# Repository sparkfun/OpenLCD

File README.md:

OpenLCD 
=========

<table class="table table-hover table-striped table-bordered">
  <tr align="center">
   <td></td>
   <td></td>
   <td></td>
  </tr>
  <tr align="center">
    <td><a href="https://www.sparkfun.com/products/14072">SparkFun 16x2 SerLCD - Black on RGB 3.3V (LCD-14072)</a></td>
    <td><a href="https://www.sparkfun.com/products/14073">SparkFun 16x2 SerLCD - RGB on Black 3.3V (LCD-14073)</a></td>
    <td><a href="https://www.sparkfun.com/products/14074">SparkFun 20x4 SerLCD - Black on RGB 3.3V (LCD-14074)</a></td>
  </tr>
</table>

These AVR-based Serial Enabled LCDs are based on the HD44780 controller, and include an AVR ATmega328P with an Arduino compatible bootloader. They accept control commands via Serial, I2C and SPI. 

This repo contains the firmware that runs on the SerLCD hardware. If you are looking for the Arduino Library to talk to these devices please go [here](https://github.com/sparkfun/SparkFun_SerLCD_Arduino_Library).

And thank you to all those that helped make OpenLCD better:

* **fourstix** - [Creating](https://github.com/sparkfun/OpenLCD/pull/13) an Arduino library to drive OpenLCD directly, added pipe character escaping
* **makinako** - [Changing](https://github.com/sparkfun/OpenLCD/pull/18) EEPROM writes to updates to reduce NVM wear and tear
* **ALittleSlow** - [Fixed](https://github.com/sparkfun/OpenLCD/pull/21) logic bug on ignoreRX

Repository Contents
-------------------
* **/Firmware**
  * **/Examples**
  * **/OpenLCD**

Documentation
--------------
* **[SparkFun SerLCD Arduino Library](https://github.com/sparkfun/SparkFun_SerLCD_Arduino_Library)** - Makes printing to and controlling the SerLCD a snap!
* **[Hookup Guide](https://learn.sparkfun.com/tutorials/avr-based-serial-enabled-lcds-hookup-guide)** - Basic hookup guide for the SparkFun Open LCD Products.
* **[SparkFun Fritzing repo](https://github.com/sparkfun/Fritzing_Parts)** - Fritzing diagrams for SparkFun products.
* **[SparkFun 3D Model repo](https://github.com/sparkfun/3D_Models)** - 3D models of SparkFun products. 
* **[SparkFun Graphical Datasheets](https://github.com/sparkfun/Graphical_Datasheets)** -Graphical Datasheets for various SparkFun products.

Product Versions
----------------
* OpenLCD
  * [LCD-14072](https://www.sparkfun.com/products/14072) - SparkFun 16x2 SerLCD - Black on RGB 3.3V
  * [LCD-14073](https://www.sparkfun.com/products/14073) - SparkFun 16x2 SerLCD - RGB on Black 3.3V
  * [LCD-14074](https://www.sparkfun.com/products/14074) - SparkFun 20x4 SerLCD - Black on RGB 3.3V

License Information
-------------------
The code is beerware; if you see me (or any other SparkFun employee) at the local, and you've found our code helpful, please buy us a round!

Distributed as-is; no warranty is given.

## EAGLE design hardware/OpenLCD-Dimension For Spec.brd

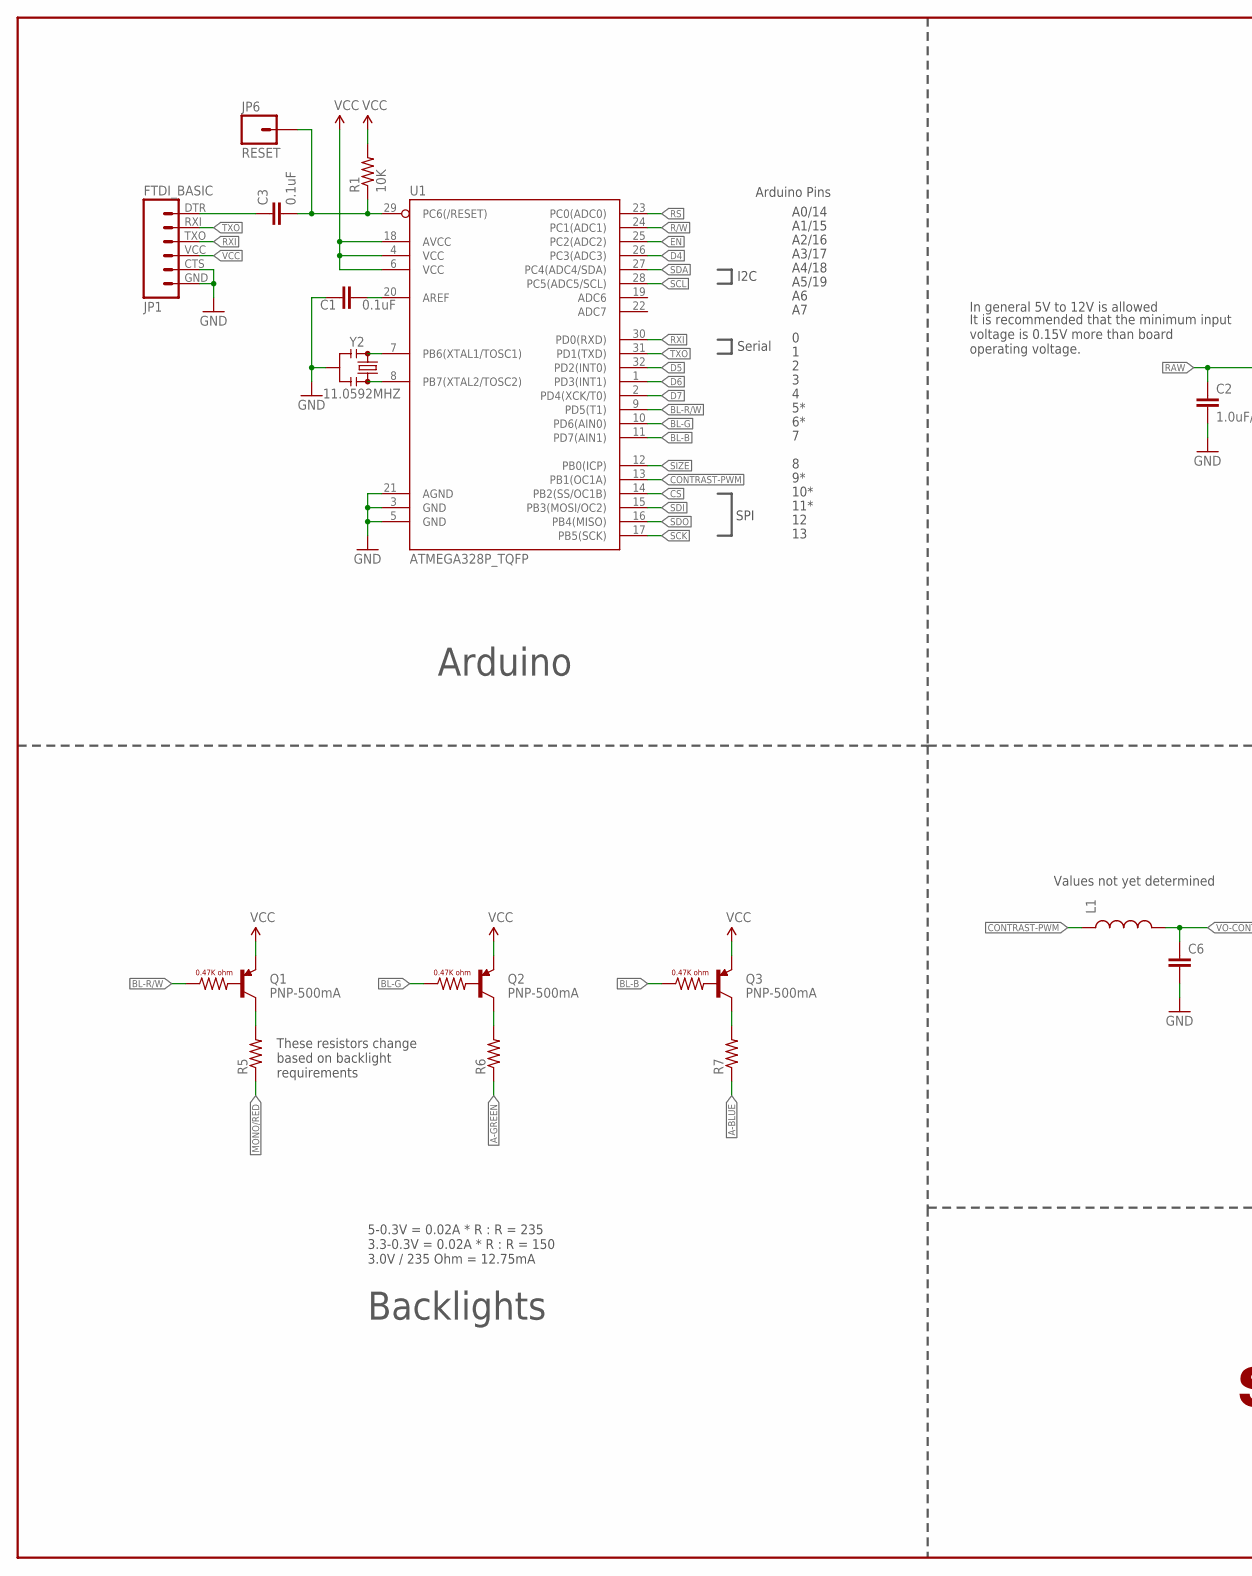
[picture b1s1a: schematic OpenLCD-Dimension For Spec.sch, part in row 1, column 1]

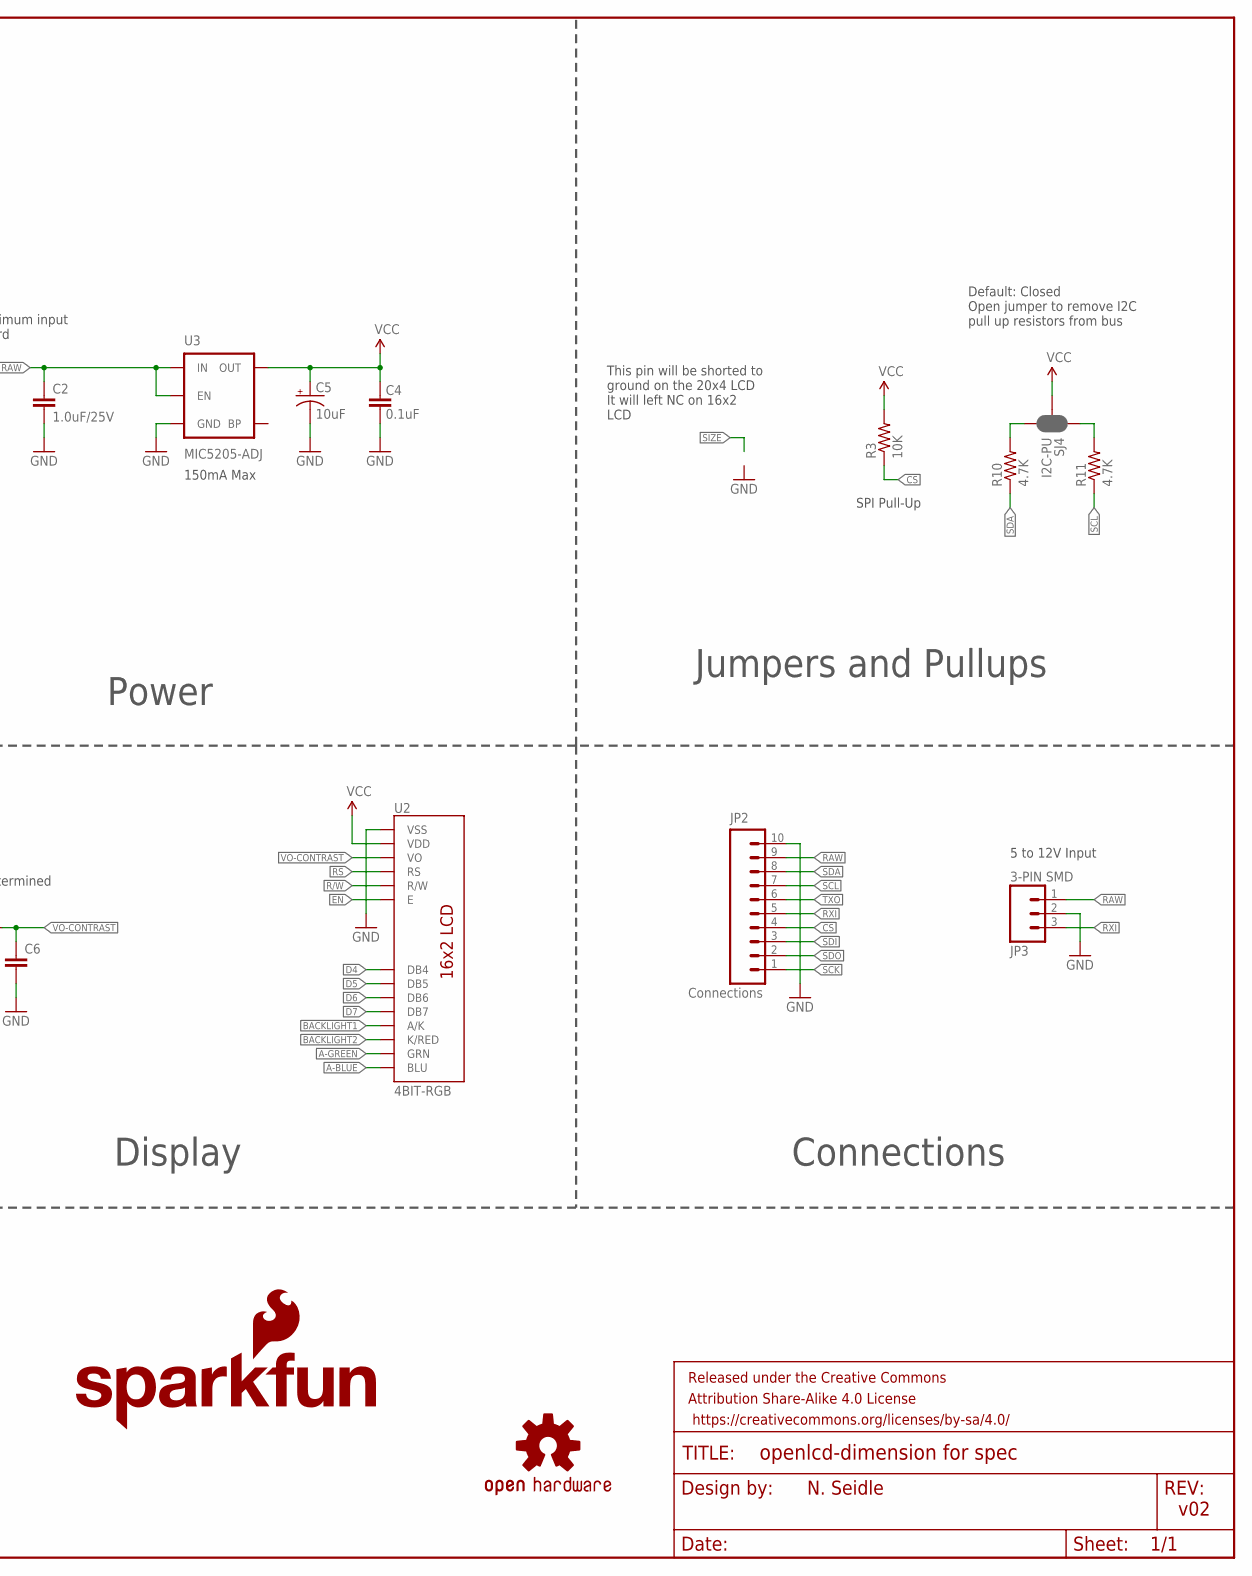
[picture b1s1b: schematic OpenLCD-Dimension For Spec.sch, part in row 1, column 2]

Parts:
C1, C3, C4: 0.1uF; 0603-CAP
C2: 1.0uF/25V; 0805-CAP
C5: 10uF; EIA3216
C6: CAP0603-CAP; 0603-CAP
FRAME1: FRAME-LEDGER; CREATIVE_COMMONS
JP1: FTDI_BASIC
JP2: Connections; 1X10
JP3: 3-PIN SMD; JST-3-PTH-VERT
JP6: RESET; 1X01
L1: INDUCTOR0603; 0603
LOGO1: SFE_LOGO_NAME_FLAME.1_INCH; SFE_LOGO_NAME_FLAME_.1
Q1, Q2, Q3: PNP-500mA; SOT23-3
R1, R3: 10K; 0603-RES
R5, R6, R7: 240; 0603-RES
R10, R11: 4.7K; 0603-RES
SJ4: I2C-PU; PAD-JUMPER-3-NC_BY_PASTE_YES_SILK_FULL_BOX
U1: ATMEGA328P_TQFP; TQFP32-08
U2: 4BIT-RGB; LCD-16X2_NOSILK-KIT-4BIT
U3: MIC5205-ADJ; SOT23-5
U$4: OSHW-LOGOS; OSHW-LOGO-S
Y2: 11.0592MHZ; RESONATOR-SMD

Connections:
!CS: JP2.4, R3.1, U1.14 (PB2(SS/OC1B))
A-BLUE: R7.1, U2.18 (BLU)
A-GREEN: R6.1, U2.17 (GRN)
AREF: C1.2, U1.20 (AREF)
BACKLIGHT1: U2.15 (A/K)
BACKLIGHT2: U2.16 (K/RED)
BL-B: Q3.1 (B), U1.11 (PD7(AIN1))
BL-G: Q2.1 (B), U1.10 (PD6(AIN0))
BL-R/W: Q1.1 (B), U1.9 (PD5(T1))
CONTRAST-PWM: L1.1, U1.13 (PB1(OC1A))
D4: U1.26 (PC3(ADC3)), U2.11 (DB4)
D5: U1.32 (PD2(INT0)), U2.12 (DB5)
D6: U1.1 (PD3(INT1)), U2.13 (DB6)
D7: U1.2 (PD4(XCK/T0)), U2.14 (DB7)
DTR: C3.1, JP1.DTR (1)
EN: U1.25 (PC2(ADC2)), U2.6 (E)
GND: C1.1, C2.2, C4.1, C5.C (-), C6.2, JP1.CTS (5), JP1.GND (6), JP2.10, JP3.2, U1.3 (GND), U1.5 (GND), U1.21 (AGND), U2.1 (VSS), U3.2 (GND), Y2.2
MONO/RED: R5.1
unnamed: Q1.3 (C), R5.2
unnamed: U1.8 (PB7(XTAL2/TOSC2)), Y2.3
unnamed: U1.7 (PB6(XTAL1/TOSC1)), Y2.1
unnamed: Q2.3 (C), R6.2
unnamed: Q3.3 (C), R7.2
unnamed: R11.2, SJ4.1
unnamed: R10.2, SJ4.3
R/W: U1.24 (PC1(ADC1)), U2.5 (R/W)
RAW: C2.1, JP2.9, JP3.1, U3.1 (IN), U3.3 (EN)
RS: U1.23 (PC0(ADC0)), U2.4 (RS)
RST: C3.2, JP6.1, R1.1, U1.29 (PC6(/RESET))
RXI: JP1.TXO (3), JP2.5, JP3.3, U1.30 (PD0(RXD))
SCK: JP2.1, U1.17 (PB5(SCK))
SCL: JP2.7, R11.1, U1.28 (PC5(ADC5/SCL))
SDA: JP2.8, R10.1, U1.27 (PC4(ADC4/SDA))
SDI: JP2.3, U1.15 (PB3(MOSI/OC2))
SDO: JP2.2, U1.16 (PB4(MISO))
SIZE: U1.12 (PB0(ICP))
TXO: JP1.RXI (2), JP2.6, U1.31 (PD1(TXD))
VCC: C4.2, C5.A (+), JP1.VCC (4), Q1.2 (E), Q2.2 (E), Q3.2 (E), R1.2, R3.2, SJ4.2, U1.4 (VCC), U1.6 (VCC), U1.18 (AVCC), U2.2 (VDD), U3.5 (OUT)
VO-CONTRAST: C6.1, L1.2, U2.3 (VO)

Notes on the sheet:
10*
11*
A0/14
A1/15
A2/16
A3/17
A4/18
A5/19
Arduino Pins
SPI
Serial
I2C
Arduino
Display
Backlights
Connections
Power
5 to 12V Input
5-0.3V = 0.02A * R : R = 235 3.3-0.3V = 0.02A * R : R = 150 3.0V / 235 Ohm = 12.75mA
SPI Pull-Up
N. Seidle
v02
Jumpers and Pullups
Default: Closed Open jumper to remove I2C pull up resistors from bus
It is recommended that the minimum input voltage is 0.15V more than board operating voltage.
In general 5V to 12V is allowed
150mA Max
Values not yet determined
These resistors change based on backlight requirements
This pin will be shorted to ground on the 20x4 LCD It will left NC on 16x2 LCD

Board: 2 copper layers, 30 parts (3 on the bottom side), 35 nets, no tracks yet.

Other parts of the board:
U$1: LOGO-SFESK; SFE-LOGO-FLAME

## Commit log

2015-02-17 Initial commit.
    Files are in an unknown state. Just getting everything moved over to new
    repo.
2015-03-11 Board layout complete
2015-03-12 Adding jumpers for size and voltage.
2015-03-18 Standard I2C interface. I2C pull ups. VCC on FTDI connector.
    Added silk to both sides. Moved contrast pin to PWM pin and direct
    connect.
2015-03-18 Final touchup before QC review.
2015-03-24 Resolved issue 1
2015-03-25 Correcting silk
2015-03-25 Updated SFE logos and flames
    To avoid extremely long CAM jobs in eagle 7.2
2015-06-16 Adding Arduino examples. Renaming main firmware.
2015-11-02 Add back contrast trimpot. Add Bypass jumper.
    Software contrast control is unreliable on too many types of LCDs.
    Returned to a trimpot. Added a bypass jumper to allow for LCDs with
    larger backlight requirements.
2015-11-03 Adding custom character support
    Doesn't work yet but getting it figured out.
2015-11-03 Connected blue backlight control pin to PWM on ATmega
2015-11-04 Added MCP4725 for contrast control. Changed to 10uF tantulum.
    We're going to try using the internal band gap reference for temp
    control and modify the contrast based on that temp. We'll see if it
    works...
2015-11-09 Fixes for issue #4.
2015-11-09 Getting closer to supporting custom characters
    Works but need to record custom chars to EEPROM and load them upon power
    up.
2015-11-11 Adding EEPROM support for custom chars. Fixing trace/space issue #4.
2017-02-21 Changes the pins to work with v2 protos. Added custom char support.
2018-07-26 Re-organized and renamed all example codes
    Pre-fixed all example sketches with "Example1_..." and so on.
    Split out communication style into sub-directories - Serial, I2C, SPI, Advanced
2018-07-26 created serial splash example code
2018-07-27 adjusting serial backlight to show all three colors more clearly
    The original example was kind of confusing in what it showed (always leaving blue ang green on 100% after a full cycle).
    This new loop shows each color individually from 0 - 50 - 100, and turns them all off at each new section.
2018-07-30 SPI example - corrected csPin, and slowed down for consistency
    Comment says D10 for cdPin, so just adjusted to match.
    At clock divide 64, it was missing a few characters here and there. It's still not perfect, but at least it's only hiccuping once in a while at clock div 128.
2018-08-02 Partial ReadMe update for going live
2018-08-02 Creating License File
2018-08-02 Formatting
2018-08-02 exported firmware HEX FILE from arduino
    Handy to have this in the repo, in case you want to upload over ISP, and for the link on the product page.
2018-08-02 cursor example update - baud to 9600 and more comments at top
    The line numbers are a little strange, so I added in a few more examples showing how to do various cursor controls to line 2, 3 and 4.
2018-08-02 Nothing to see here
    clearing out some stuff from product development and various design phases
2018-08-02 removing unnecessary and confusing files
2018-08-03 removing note about hardware CC license
2018-08-21 Add files via upload
    Fixed a bug (Fence Post error) in the Display Customer character command that allowed the user to request a ninth character when only 8 are allowed. The upper limit in the if statement was off by one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
2018-08-24 Add logic to print pipe if second control chracter is read
    This allows the user to print a pipe control character to the display by escaping the control character as a double pipe
2018-08-28 Add function to set backlight to RGB value without flickering
2018-08-28 Fix size of array and add demo of new command
2018-08-28 Fix comment and add missing debug statements to demo code
2018-08-28 Changing I2C backlight example to show new method. Removing dead/old advanced sketches. Updating cheatsheet in examples.
2018-08-28 Removing old comments.
2018-09-02 Create OpenLCD library
2018-09-15 Simplifying mode logic
    This reduces the decision tree time a bit.
2018-09-15 Removing OLED functions
    We thought about OLEDs for a bit, now committed to 16x2 and 20x4 LCDs.
2018-09-15 Adding firmware version to boot screen
2018-09-15 Adding display firmware version
2018-09-15 Change order in which version is printed
2018-09-16 Fixed 'display firmware' command. It was overlapping on custom chars.
2019-01-30 Updated all references of EEPROM.write to EEPROM.update
    Patch to reduce unnecessary EEPROM writes by using .update() method, which compares the current value. The comparatively small cost of the read should be more than made up for by the reduction in wri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
2019-01-31 Add whitespace to header comments to get linker to work
    Without these extra spaces the sketch fails to compile because the pre-processor doesn't correctly create the prototypes of functions in the tabs.
2019-02-12 Created combined hex of current firmware
    for production programming
2019-02-12 removing blank writes in combined hex file
2019-02-12 copying recent combined hex over old file name
    this will allow for links to stay the same in all documentation
2019-02-15 Add system message control
2019-02-16 Adding system message enable/disable. Add discrete enable/disable splash commands.
2019-02-16 Add comment
2019-02-16 Add link to library
2019-03-17 Update OpenLCD.ino
    Add custom firmware sub-minor version.
    Disable SPI.
2019-03-17 Update Setting_Control.ino
    Fix bug in reporting settingIgnoreRX. Logic was backward.
    Label red brightness as Red, not Brightness.
2019-03-17 Update settings.h
    Separate default brightness into Red, Green and Blue brightnesses.
    Customize default values for Solar Stik.
2019-03-17 Fix bug which disabled emergency reset; customizations
    1) remove conditional code that could never be true
    2) customize boot screen
    3) initialize settingIgnoreRX to false vs. 0xFF
2019-03-17 Fix bug which disables emergency reset by default
    Initialize settingIgnoreRX to false.
    In emergency reset, use default value for contrast instead of literal, and set brightnesses to defaults.
2019-03-17 Split DEFAULT_BRIGHTNESS into red, green and blue
    exchange DEFAULT_BRIGHTNESS for
    DEFAULT_RED, DEFAULT_GREEN and DEFAULT_BLUE
2019-03-17 Fix backward logic displaying settingIgnoreRX
2019-03-17 remove debug line
2019-03-18 Bumping version after PR #21
2019-03-18 Adding thank yous
2019-03-19 enable true off for blue LED
    SoftPWM has a true off (0 is really off), but not a true on (255 is not 100% duty cycle), so invert the logic to be able to fully turn off the blue LED.
2020-02-18 bumping version to v14 after PR #22
    Also added notes at header comments showing changes for v13 and v14
2022-04-08 Added support for directly controlling a SparkFun Qwiic Twist - RGB Rotary Encoder Breakout https://www.sparkfun.com/products/15083
    New feature to set serLCD TWI mode as host, allowing Twist to be directly polled by serLCD.
    Useful when the serLCD is controlled by a host's UART.
    Example: a python script on a PC using a Basic Breakout, where the Qwiic is directly connected between the serLCD and the Twist.
    New Command codes.
    50 Enables the twist streaming. Any Twist change prints the event.
    51 Disables the twist streaming

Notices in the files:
parts and their libraries:
SparkFun-DiscreteSemi: Licensing: CC v3.0 Share-Alike You are welcome to use this library for commercial purposes.
SparkFun-Aesthetics: Released under the Creative Commons Attribution Share-Alike 4.0 License
SparkFun-Aesthetics: https://creativecommons.org/licenses/by-sa/4.0
